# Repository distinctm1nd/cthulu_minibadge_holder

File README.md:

# Cthulu Minibadge Holder

*"In his house at R'lyeh, dead Cthulhu waits dreaming."*

## Assembly Instructions

You should have the following items:

- Badge PCB
- (12) 8 pin headers
- (6) Minibadge kits
- 3D printed monolith badge stand
- Sticker
- Instruction book

The Cthulu Minibadge Holder is mostly assembled. The only required assembly is to solder the 12 minibadge headers to the front. Be careful while soldering these that you don't damage any of the components on the back.

Power on by connecting to USB and verifying that the switch is in the lower position. Try to use a low profile USB connector so that the minibadge holder sits level in the monolith stand.

## Operating Instructions

The minibadge holder has three LED groups:

- the eyes (2 LEDs)
- the sigil (9 LEDs)
- the tentacle curls (8 LEDs)

It has one button, and everything is done with taps and holds.

A new or reset badge starts on the Cthulhu Awakens Scene (scenes are listed below). When the badge is powered off all custom settings are saved.

### Button Controls

| Action | What it does |
| --- | --- |
| Short press | Next scene. A row of LEDs shows the scene number, white, or yellow if the scene is a favourite. |
| Hold (0.8 s) | Open the Theme Menu. |
| 1 tap + hold | Open the Settings Menu. |
| 2 taps + hold | Marks or unmarks the current scene as a favorite. Green blink = added, red blink = removed. |
| 3 taps + hold | Start auto-cycling (see below). |
| 4 taps + hold | Play the Morse message on the eyes ("IA IA CTHULHU FHTAGN"). Any press stops it. |
| 5 quick taps | Play The Cthulhu Awakens show with lightning (12 s). |

"Tap + hold" means tap quickly, then hold on the last tap.

### Scene number display

- Scenes 1–17 light that many LEDs.
- Above 17, all 17 LEDs light up. The white or yellow ones count how far past 17 you are, and the rest are teal.
- The menus use the same display for palette and animation numbers.

### Auto-cycling

Auto-cycling switches scenes by itself. There's not a menu for it. You set it with 3 taps + hold: tap quickly three times, then hold the button down at least 0.8s. Each time you do this, the badge moves to the next step:

| Step | Blinks | Switches scene every |
| --- | --- | --- |
| Off | 2 red | never |
| 1 | 1 green | 4 seconds |
| 2 | 2 green | 8 seconds |
| 3 | 3 green | 20 seconds |
| 4 | 4 green | 60 seconds |

After step 4, the next 3 taps + hold turns it off again, and the steps repeat.

- **Which scenes:** it cycles through scenes that have been marked as favorites. If you haven't marked any, it cycles through every scene.
- **To stop it:** one short press stays on the scene you're looking at and stops the cycling. You can also keep stepping with 3 taps + hold until you reach off.
- **To take a scene out of the cycle:** unmark it with 2 taps + hold.
- **Saved:** the step you choose is kept when the badge is powered off.

### LED Scenes

| # | Scenes |
| --- | --- |
| 1–15 | Cthulhu Rises, Sleeping in R'lyeh, The Deep Ones, Abyssal Tide, Shadow over Innsmouth, Call of Cthulhu, Great Old One, Elder Gods, When the Stars Are Right, Eldritch Spectrum, Dagon, Nyarlathotep, Yog-Sothoth, Necronomicon, Starry Wisdom |
| 16–25 (slow) | Dreaming in R'lyeh, The Drowned City, Sunken Fire, Deep Ones' Lullaby, Cosmic Drift, Madness Creeping, The Watcher in the Deep, Elder Sign, Crimson Stare, The Slow Awakening |
| 26–31 (special effects) | Ripples of R'lyeh, Crashing Waves, Whisperer in Darkness, The Twin Cults, Pulse of Elder Things, Cthulhu Stirs |
| 32 | Cthulhu Awakens |
| 33 | The Yellow Sign |
| 34 | CUSTOM (your own theme.. ) |

Every scene also has some extra effects built in:

- **Twinkle:** random LEDs flare like stars.
- **Fade:** a slow wave of dimming and brightening.
- **Surge:** the animation speeds up and slows down every 10 s or so.
- **Slower:** scenes 1–15 and 26–31 run slower than the base speed.
- **Lightning:** scenes 4 and 28, and the 5-tap show. In the two scenes it strikes when you pick the scene, then once every 2–4 minutes. In the 5-tap show it strikes often.

### Menus

- Short press changes the value on the current page.
- Hold goes to the next page. After the last page the menu closes and your choices are saved.
- If you press nothing for 15 seconds, the menu closes and saves.

### Scene Menu (Hold 0.8 sec)

This menu changes CUSTOM only. On entry, a row of blue LEDs shows the page number (every 5th LED is magenta to help you count). The block (ex: Eye LEDs) you're editing stays bright and the others dim.

When you enter the CUSTOM menu, the current scene is copied into the CUSTOM slot. You can then edit it directly and it will automatically save.

Use a short press to move through the menu options. For instance, if on Page 1 (eyes palette) you'll see the eye LED colors change as you cycle through them via short button presses. To move to the next page; hold the button (0.8 seconds). All pages are listed below. There is a page for each LED block color and animation / effects. So you'll edit each one individually as you step through the pages.

| Page | Edits |
| --- | --- |
| 1 | Eyes palette |
| 2 | Eyes animation |
| 3 | Sigil palette |
| 4 | Sigil animation |
| 5 | Tentacle Curls palette |
| 6 | Tentacle Curls animation |

- Palette pages show the palette as a steady swatch, one colour per LED.
- Animation pages play the animation live.
- Choosing Storm (lightning) fires one strike straight away so you can see it took. In normal running it still strikes only every few minutes.

#### Palette options (press to step through; wraps back to 1)

1. Great Old One: reds, olive-greens, yellow
2. Call of Cthulhu: reds, bright to deep, yellow
3. Shadow over Innsmouth: sky blue to deep blue, red
4. The Deep Ones: greens, light to dark, yellow
5. Abyssal Tide: pale aqua, blues, white
6. Elder Gods: reds, bright to deep, dark red-brown
7. When the Stars Are Right: oranges, white
8. Eldritch Spectrum: red, yellow, orange, teal
9. Cthulhu Rises: red, green, blue, orange, teal
10. Sleeping in R'lyeh: blues, light to deep, white
11. Cthulhu Awakened: teal, Cthulhu green, sea green, deep teal, pale aqua

#### Animation options (press to step through; wraps back to 1)

1. Drift: the original scrolling palette
2. Slumber: slow breathing
3. Rising tide: a wave of brightness rolls down the tentacles
4. Storm: dim glow with lightning
5. Stars: random twinkling
6. Watchful blink: normal glow that blinks off now and then
7. Heartbeat: slow double "lub-dub" pulse
8. Comet: a bright comet with a fading tail
9. Ember: smooth random flicker, like embers
10. Aurora: two slow waves of light drifting through each other
11. Scanner: a bright dot sweeps back and forth
12. Fairy: every other LED swaps on and off
13. Swell: one huge slow ocean swell
14. Crossfade: slowly melts from one palette colour to the next
15. Currents: a smooth gradient of palette colours flows along
16. Fog: dim, slow, overlapping waves, like mist
17. Gaze: slowly opens, holds, slowly closes (eyes take turns)
18. Ripple: soft rings spread out from the middle of the tentacles
19. Surf: waves crash in with a bright edge and drain away
20. Twin comets: two comets run in opposite directions and pass through each other
21. Glitch: dim static with random bright flashes
22. Dim: a dim, slowly breathing glow
23. Bloom: soft rings spread out from the middle of the sigil
24. Spin: a bright segment circles round the 9 sigil LEDs

Animations 14–19 also blend smoothly between the palette colours.

### Settings Menu (1 tap + hold)

These settings apply to all scenes, not just CUSTOM. On entry, a row of orange LEDs shows the page number. The value shows as a row of white LEDs, where 1 LED means the first level. As before, short press to cycle through each page option, and long press to go to the next page. For example, if you want to change the speed to fast you would: Long Press (enter Page 1 - brightness), Long Press (enter Page 2 - Eye Brightness), Long Press (enter Page 3 - Speed). Short Press to step from Normal Speed to Fast Speed. Long Press to exit menu or let it time out in 15 seconds.

| Page | Setting | Levels (default in bold) |
| --- | --- | --- |
| 1 | Brightness (all LEDs) | 1 = **brightest**, 2, 3, 4 = dimmest |
| 2 | Eye brightness (relative to the rest) | 1 = **same as the rest**, 2, 3, 4 = dimmest |
| 3 | Speed | 1 = slow, 2 = **normal**, 3 = fast |

### Power-up reset

1. Hold the button while plugging the badge in.
2. After 8 seconds the eyes turn red.
3. Let go. Everything resets to default, including favourites, CUSTOM and the settings, and the badge blinks green 3 times.

If you let go before 8 seconds, the badge just starts normally.

## Programming

The microcontroller is an Attiny814. You can program using the 3-pin sneaky connector (doesn't require soldering).

- Pin 1: Power
- Pin 2: UDPI
- Pin 3: Ground

There are multiple ways to program so if you already have your method then you are good to go. If you have not programmed an ATtiny with UDPI then I recommend following the instructions located here to get started: https://wolles-elektronikkiste.de/en/using-megatinycore.

If you use the method described here with Arduino, you do not need to connect a resistor in series with pin 6 because this is already installed on the board.

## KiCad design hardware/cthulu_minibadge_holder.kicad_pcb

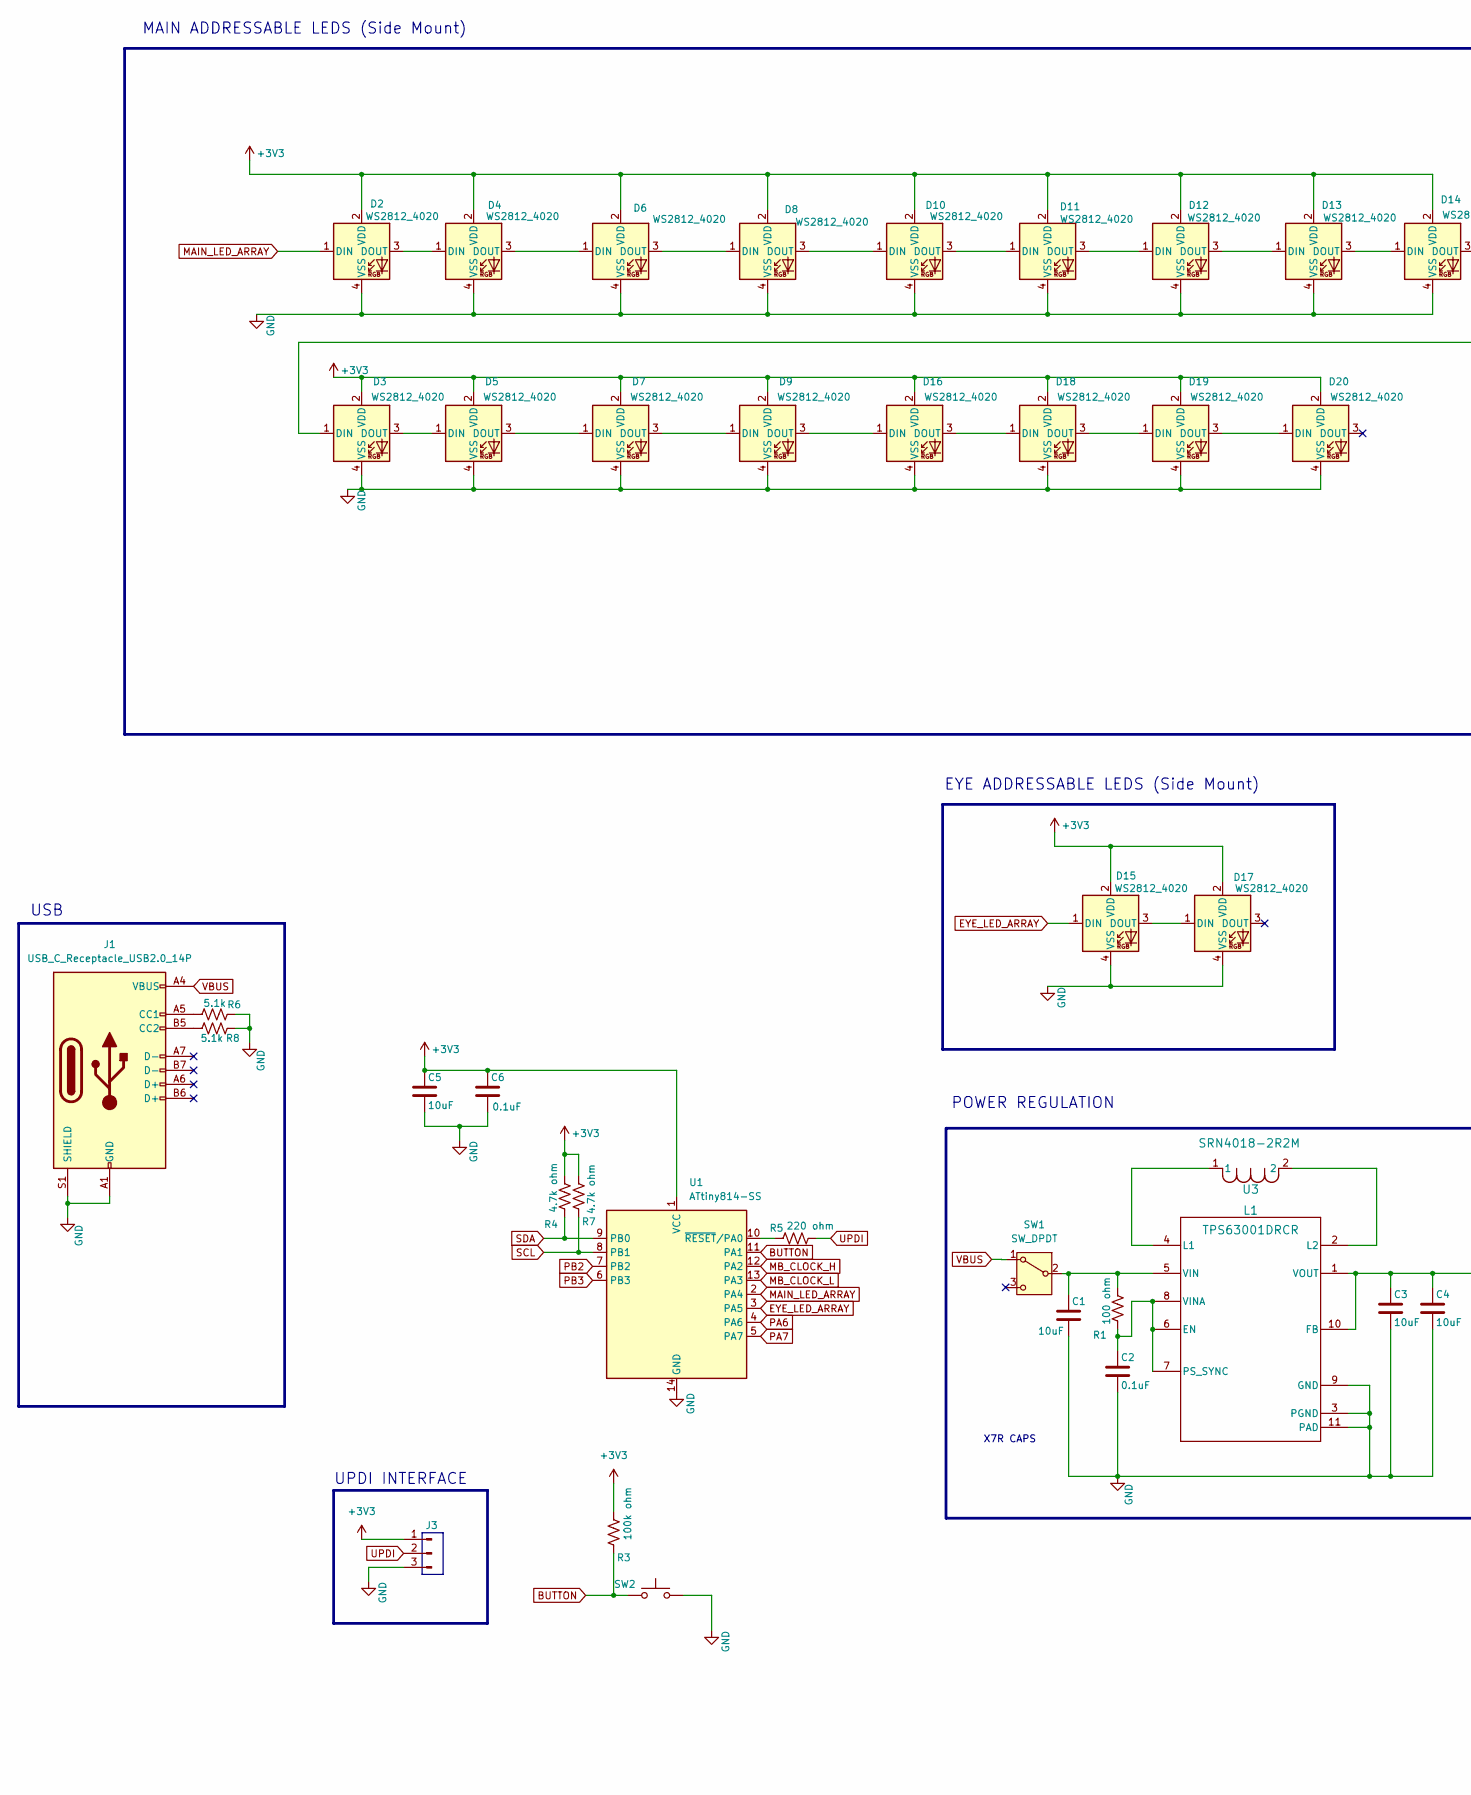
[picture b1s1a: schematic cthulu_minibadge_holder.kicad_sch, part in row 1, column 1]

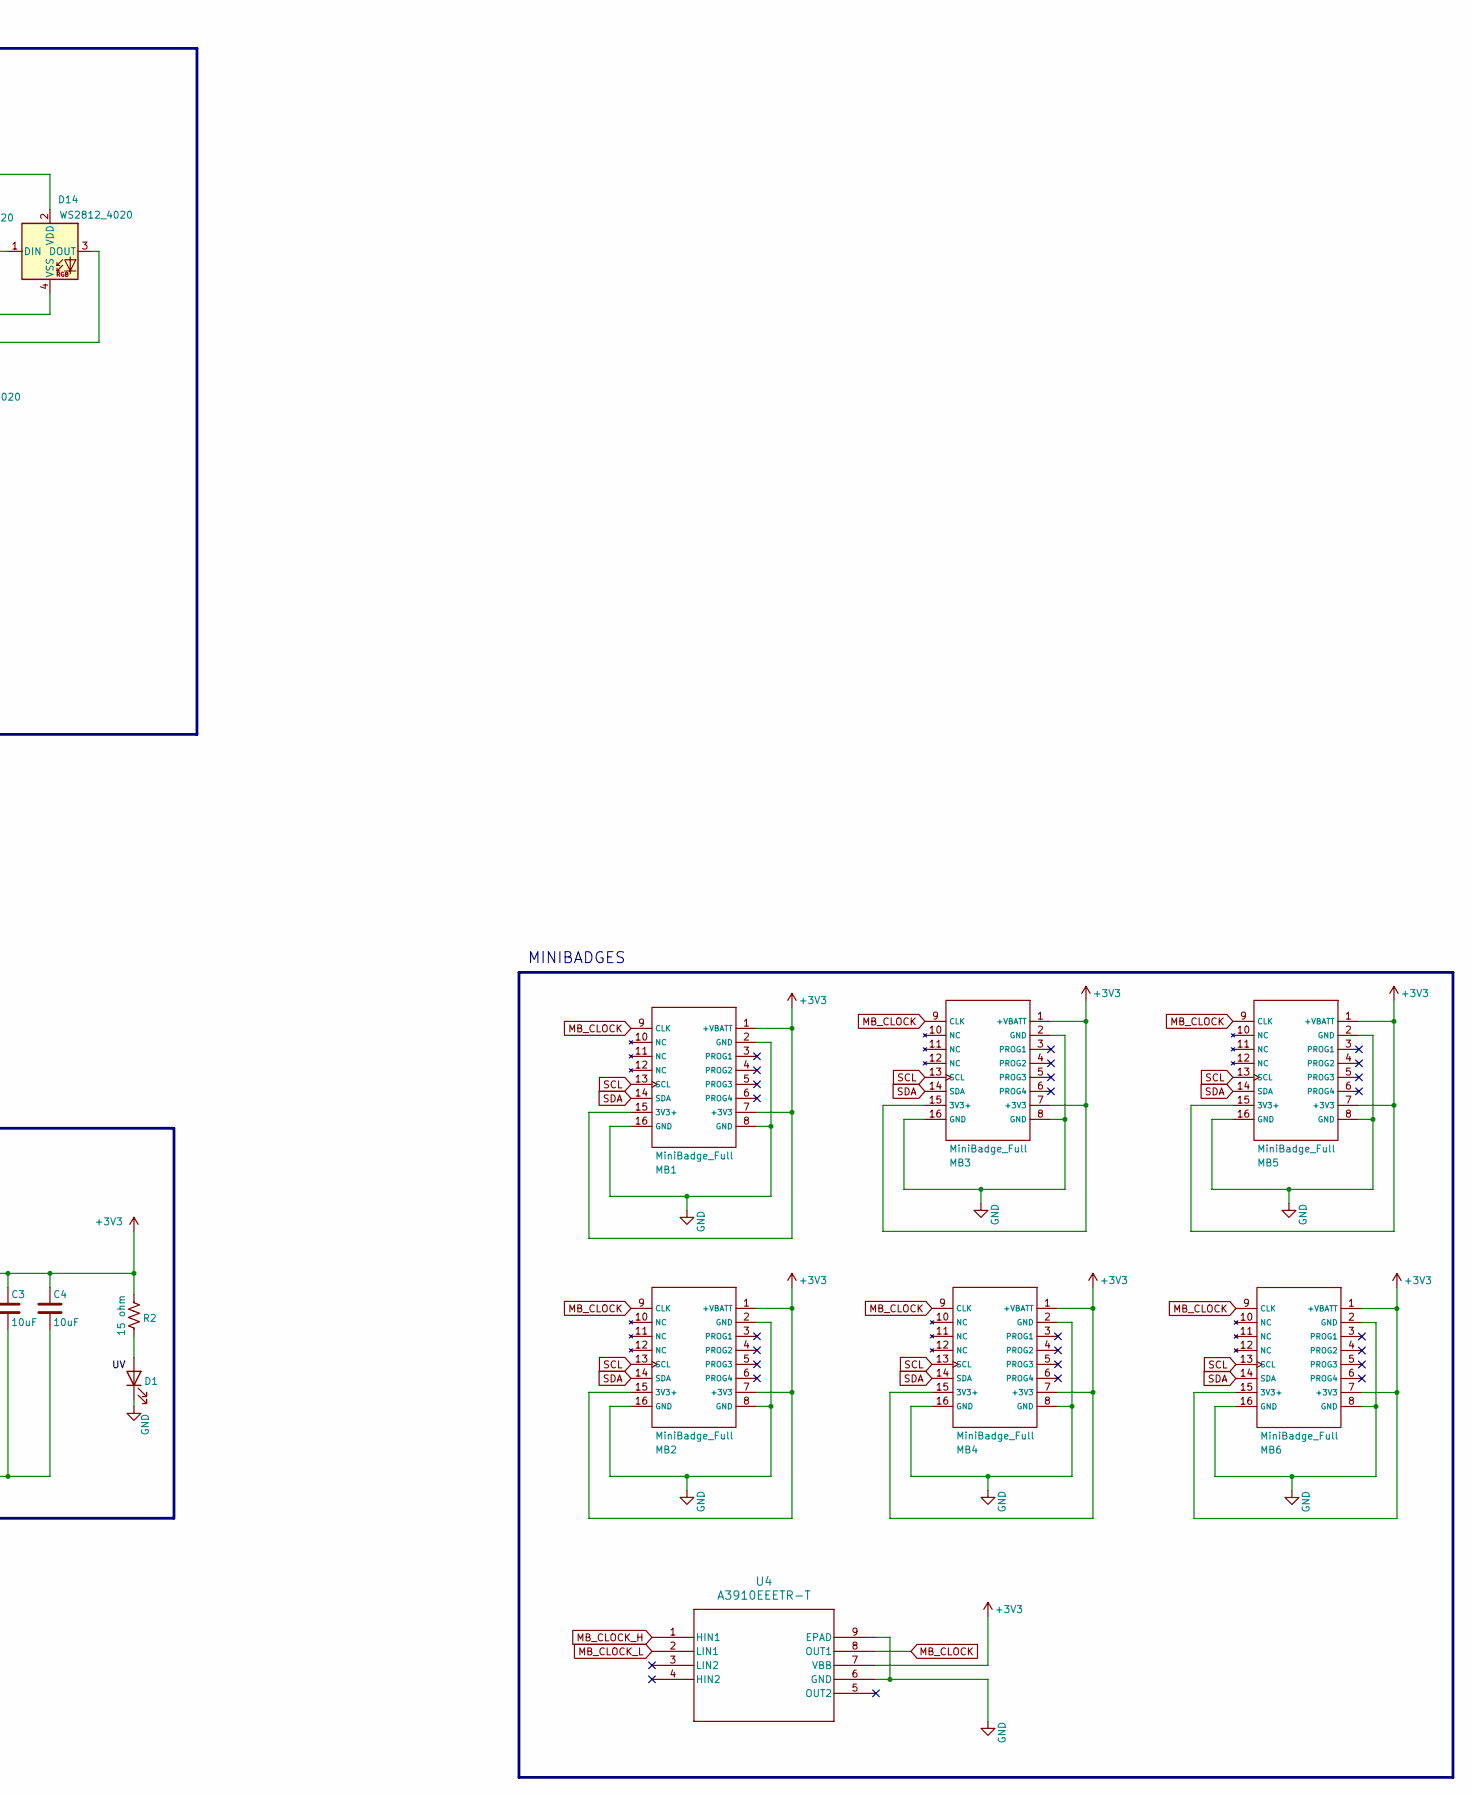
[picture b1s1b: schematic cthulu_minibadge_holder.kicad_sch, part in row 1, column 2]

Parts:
C1, C3, C4, C5: 10uF; C_0805_2012Metric_Pad1.18x1.45mm_HandSolder
C2, C6: 0.1uF; C_0603_1608Metric_Pad1.08x0.95mm_HandSolder
D1: LED; LED_1206_3216Metric_Pad1.42x1.75mm_HandSolder
D2, D3, D4, D5, D6, D7, D8, D9, D10, D11, D12, D13, D14, D15, D16, D17, D18, D19, D20: WS2812_4020; sk6812-side-a
J1: USB_C_Receptacle_USB2.0_14P; USB_C_Receptacle_GCT_USB4125-xx-x-0190_6P_TopMnt_Horizontal
J3: Conn_01x03_Pin; night_evil_ai_updi
L1: SRN4018-2R2M; L_Bourns-SRN4018
MB1, MB2, MB3, MB4, MB5, MB6: MiniBadge_Full; MiniBadge_Slot_Basic
R1: 100 ohm; R_0603_1608Metric_Pad0.98x0.95mm_HandSolder
R2: 15 ohm; R_0603_1608Metric_Pad0.98x0.95mm_HandSolder
R3: 100k ohm; R_0603_1608Metric_Pad0.98x0.95mm_HandSolder
R4, R7: 4.7k ohm; R_0603_1608Metric_Pad0.98x0.95mm_HandSolder
R5: 220 ohm; R_0603_1608Metric_Pad0.98x0.95mm_HandSolder
R6, R8: 5.1k; R_0603_1608Metric_Pad0.98x0.95mm_HandSolder
SW1: SW_DPDT; js202011jaqn
SW2: SW_Push; button_switch_TL3305A
U1: ATtiny814-SS; SOIC-14_3.9x8.7mm_P1.27mm
U3: TPS63001DRCR; Texas_DRC0010J
U4: A3910EEETR-T; DFN-8_ALM

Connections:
+3V3: C3.1, C4.1, C5.1, C6.1, D2.2 (VDD), D3.2 (VDD), D4.2 (VDD), D5.2 (VDD), D6.2 (VDD), D7.2 (VDD), D8.2 (VDD), D9.2 (VDD), D10.2 (VDD), D11.2 (VDD), D12.2 (VDD), D13.2 (VDD), D14.2 (VDD), D15.2 (VDD), D16.2 (VDD), D17.2 (VDD), D18.2 (VDD), D19.2 (VDD), D20.2 (VDD), J3.1, MB1.1 (+VBATT), MB1.7 (+3V3), MB1.15 (3V3+), MB2.1 (+VBATT), MB2.7 (+3V3), MB2.15 (3V3+), MB3.1 (+VBATT), MB3.7 (+3V3), MB3.15 (3V3+), MB4.1 (+VBATT), MB4.7 (+3V3), MB4.15 (3V3+), MB5.1 (+VBATT), MB5.7 (+3V3), MB5.15 (3V3+), MB6.1 (+VBATT), MB6.7 (+3V3), MB6.15 (3V3+), R2.1, R3.1, R4.1, R7.1, U1.1 (VCC), U3.1 (VOUT), U3.10 (FB), U4.7 (VBB)
BUTTON: R3.2, SW2.1, U1.11 (PA1)
EYE_LED_ARRAY: D15.1 (DIN), U1.3 (PA5)
GND: C1.2, C2.2, C3.2, C4.2, C5.2, C6.2, D1.1 (K), D2.4 (VSS), D3.4 (VSS), D4.4 (VSS), D5.4 (VSS), D6.4 (VSS), D7.4 (VSS), D8.4 (VSS), D9.4 (VSS), D10.4 (VSS), D11.4 (VSS), D12.4 (VSS), D13.4 (VSS), D14.4 (VSS), D15.4 (VSS), D16.4 (VSS), D17.4 (VSS), D18.4 (VSS), D19.4 (VSS), D20.4 (VSS), J1.A1 (GND), J1.A12 (GND), J1.B1 (GND), J1.B12 (GND), J1.S1 (SHIELD), J3.3, MB1.2 (GND), MB1.8 (GND), MB1.16 (GND), MB2.2 (GND), MB2.8 (GND), MB2.16 (GND), MB3.2 (GND), MB3.8 (GND), MB3.16 (GND), MB4.2 (GND), MB4.8 (GND), MB4.16 (GND), MB5.2 (GND), MB5.8 (GND), MB5.16 (GND), MB6.2 (GND), MB6.8 (GND), MB6.16 (GND), R6.1, R8.1, SW2.2, U1.14 (GND), U3.3 (PGND), U3.9 (GND), U3.11 (PAD), U4.6 (GND), U4.9 (EPAD)
MAIN_LED_ARRAY: D2.1 (DIN), U1.2 (PA4)
MB_CLOCK: MB1.9 (CLK), MB2.9 (CLK), MB3.9 (CLK), MB4.9 (CLK), MB5.9 (CLK), MB6.9 (CLK), U4.8 (OUT1)
MB_CLOCK_H: U1.12 (PA2), U4.1 (HIN1)
MB_CLOCK_L: U1.13 (PA3), U4.2 (LIN1)
unnamed: D1.2 (A), R2.2
unnamed: D2.3 (DOUT), D4.1 (DIN)
unnamed: D3.3 (DOUT), D5.1 (DIN)
unnamed: D4.3 (DOUT), D6.1 (DIN)
unnamed: D5.3 (DOUT), D7.1 (DIN)
unnamed: D6.3 (DOUT), D8.1 (DIN)
unnamed: D7.3 (DOUT), D9.1 (DIN)
unnamed: D8.3 (DOUT), D10.1 (DIN)
unnamed: D10.3 (DOUT), D11.1 (DIN)
unnamed: D11.3 (DOUT), D12.1 (DIN)
unnamed: D12.3 (DOUT), D13.1 (DIN)
unnamed: D13.3 (DOUT), D14.1 (DIN)
unnamed: D3.1 (DIN), D14.3 (DOUT)
unnamed: D15.3 (DOUT), D17.1 (DIN)
unnamed: D9.3 (DOUT), D16.1 (DIN)
unnamed: D16.3 (DOUT), D18.1 (DIN)
unnamed: D18.3 (DOUT), D19.1 (DIN)
unnamed: D19.3 (DOUT), D20.1 (DIN)
unnamed: J1.A5 (CC1), R6.2
unnamed: J1.B5 (CC2), R8.2
unnamed: C1.1, R1.1, SW1.2 (B), U3.5 (VIN)
unnamed: R5.2, U1.10 (~RESET/PA0)
unnamed: C2.1, R1.2, U3.6 (EN), U3.7 (PS_SYNC), U3.8 (VINA)
unnamed: L1.1, U3.4 (L1)
unnamed: L1.2, U3.2 (L2)
PA6: U1.4 (PA6)
PA7: U1.5 (PA7)
PB2: U1.7 (PB2)
PB3: U1.6 (PB3)
SCL: MB1.13 (SCL), MB2.13 (SCL), MB3.13 (SCL), MB4.13 (SCL), MB5.13 (SCL), MB6.13 (SCL), R7.2, U1.8 (PB1)
SDA: MB1.14 (SDA), MB2.14 (SDA), MB3.14 (SDA), MB4.14 (SDA), MB5.14 (SDA), MB6.14 (SDA), R4.2, U1.9 (PB0)
UPDI: J3.2, R5.1
VBUS: J1.A4 (VBUS), J1.A9 (VBUS), J1.B4 (VBUS), J1.B9 (VBUS), SW1.1 (A)

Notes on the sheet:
UPDI INTERFACE
POWER REGULATION
MINIBADGES
X7R CAPS
MAIN ADDRESSABLE LEDS (Side Mount)
EYE ADDRESSABLE LEDS (Side Mount)
USB

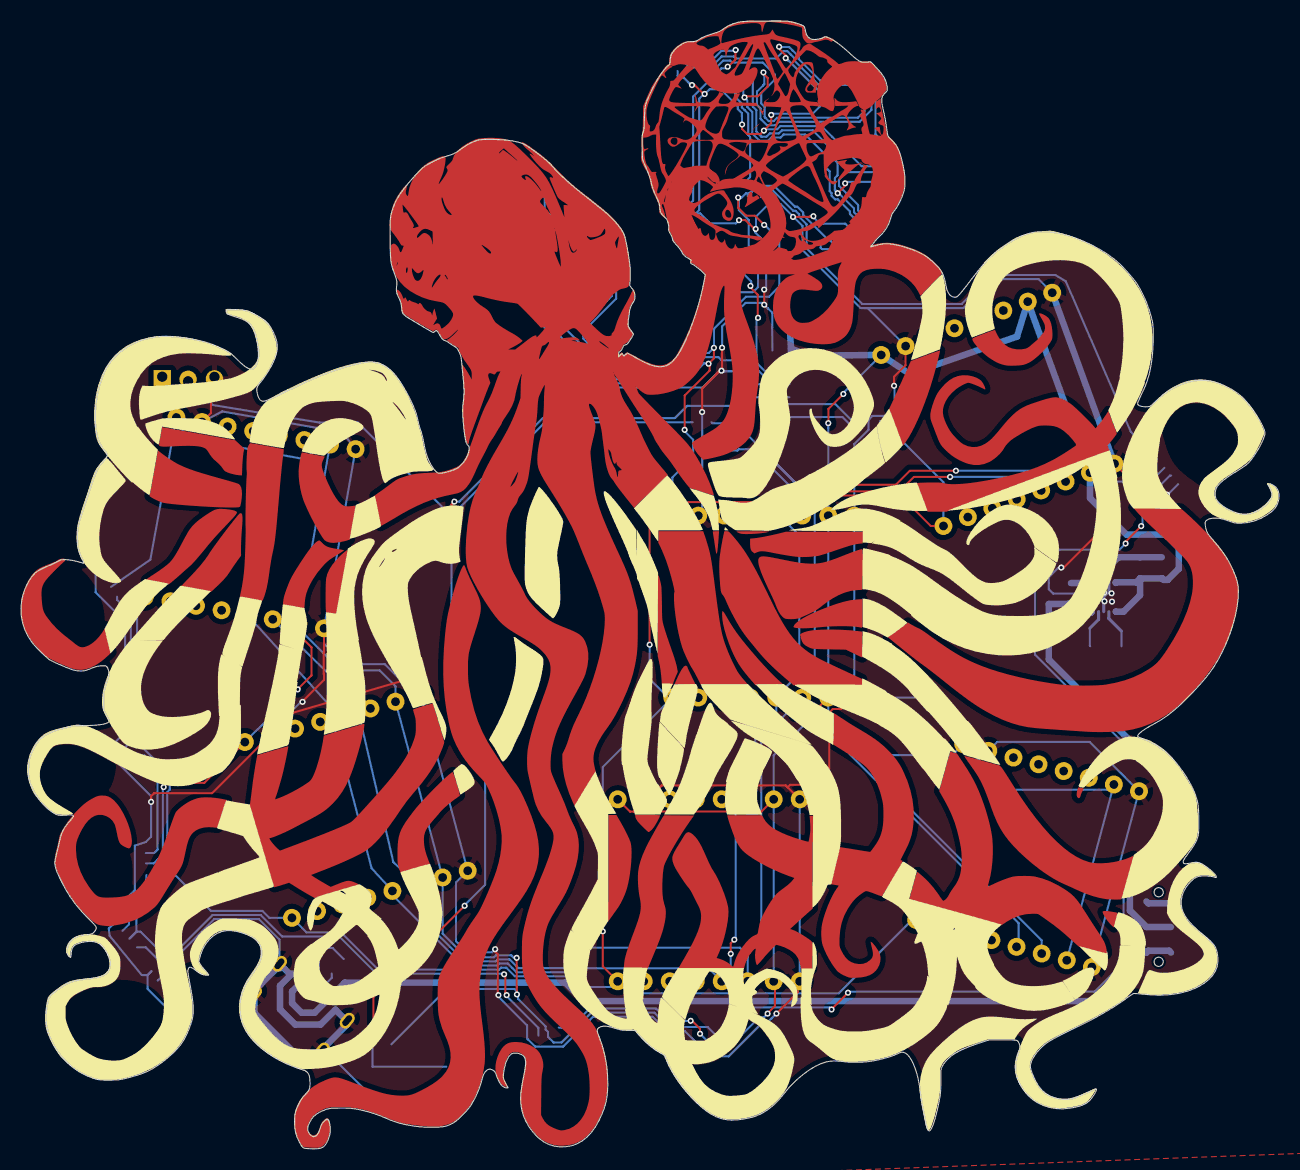
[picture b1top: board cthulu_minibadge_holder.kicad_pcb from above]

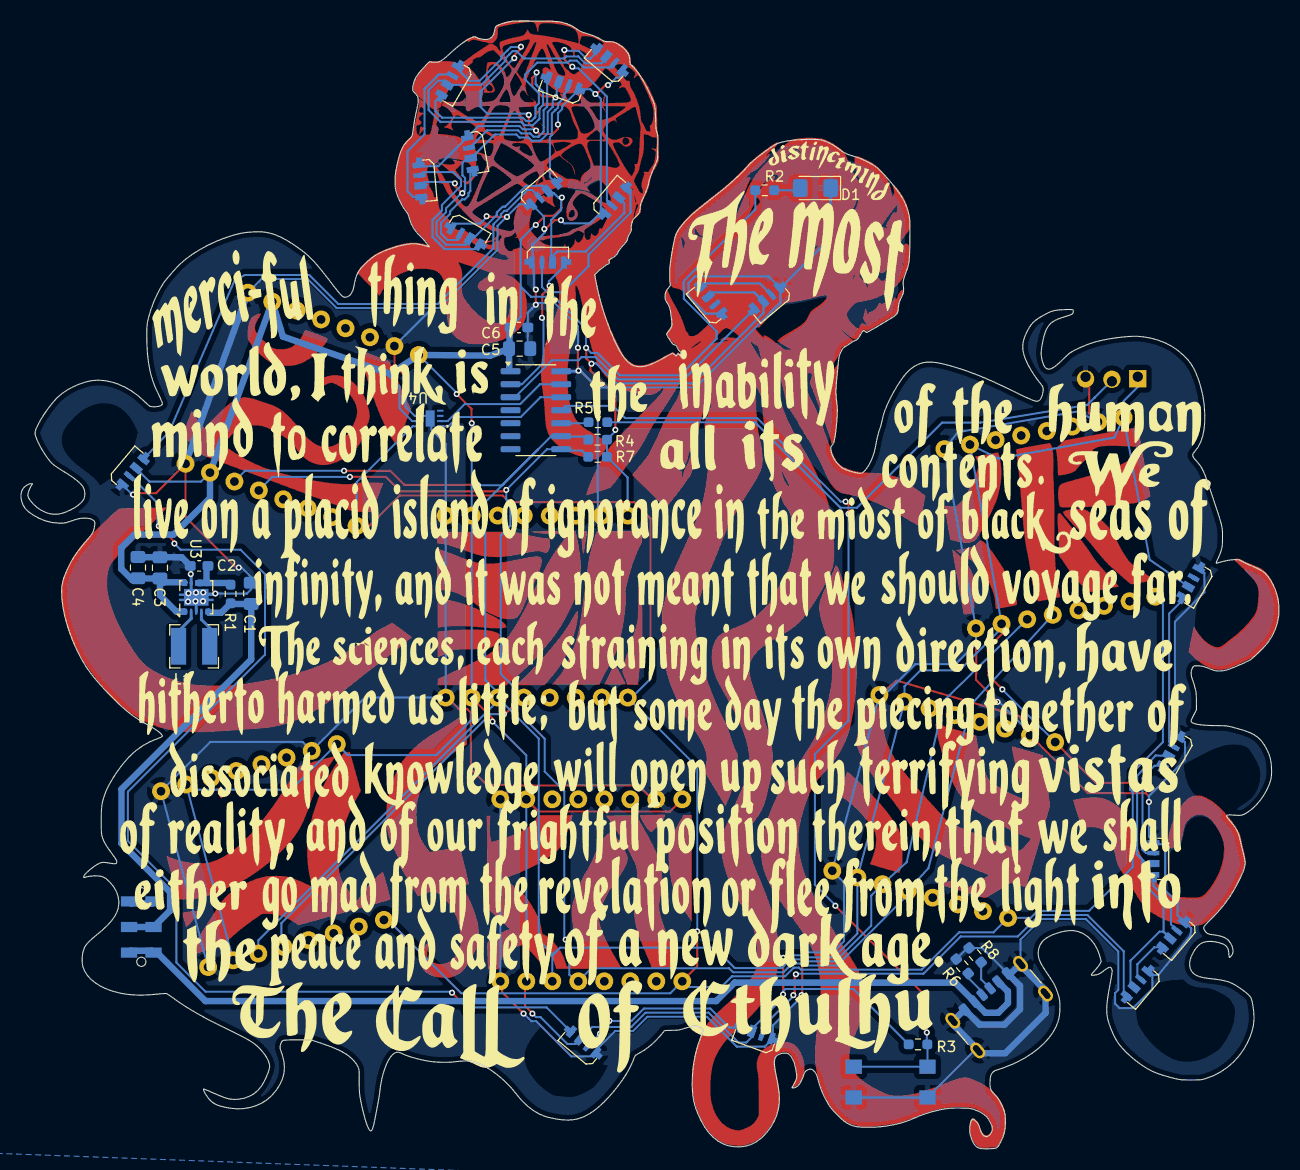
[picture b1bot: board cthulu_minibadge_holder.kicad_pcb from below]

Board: 2 copper layers, 122.9 x 110.2 mm, 48 parts (42 on the bottom side), 37 nets.
